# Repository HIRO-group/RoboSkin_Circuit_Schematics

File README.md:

# Robo-Skin Circuit Schematics

Below is the schematic file:

Below is the Board file:

The gerber files will be in the CamOutput folder. The .sch file is the eagle schematics and .brd is the board file. 

The schematics contain circuit in human readable format

The board files contain circuit which can be etched on a copper sheet, basically the final how circuit board looks like

You can install final gerber files like this:

```bash
sudo apt install gerbv
gerbv GERBER_FILE_PATH
```

Modifications and suggestions are highly appreciated. Be sure to give a PR.

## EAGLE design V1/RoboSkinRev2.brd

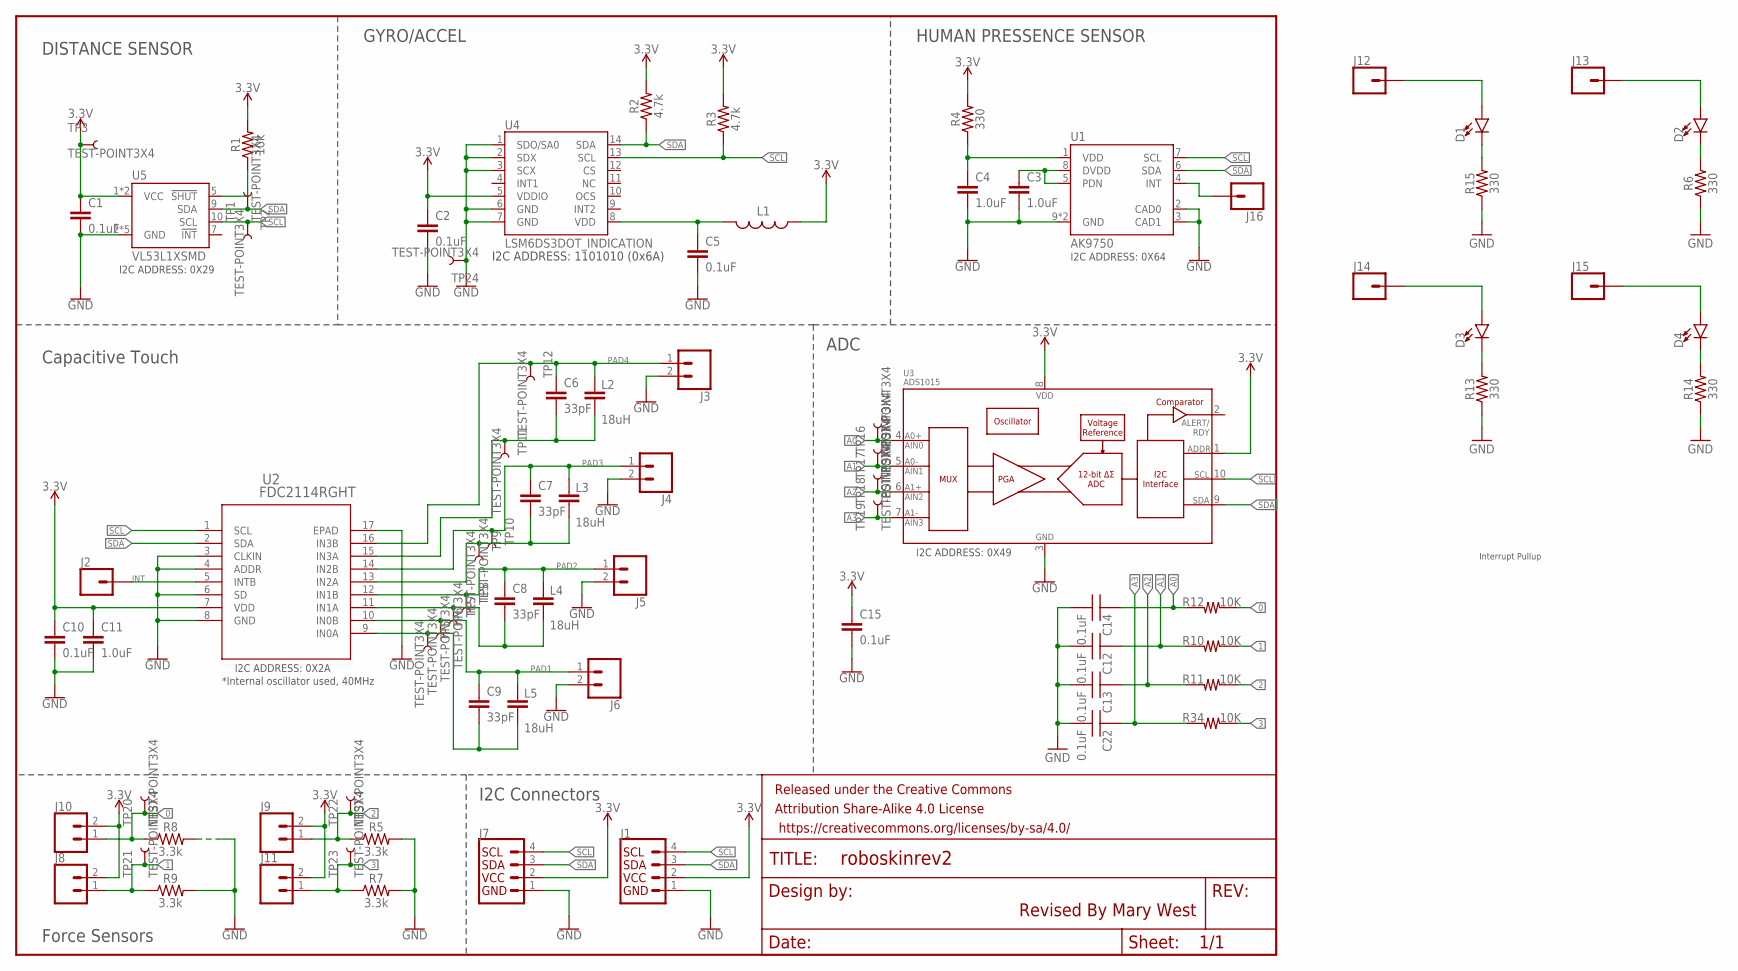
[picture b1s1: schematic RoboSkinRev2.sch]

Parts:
C1, C2, C5, C10, C15: 0.1uF; 0603
C3, C4, C11: 1.0uF; 0603
C6, C7, C8, C9: 33pF; 0603
C12, C13, C14, C22: 0.1uF; 0603_SILK; PARTNO GRM188R70J104KA01D
D1, D2, D3, D4: LED1206; LED-1206
FRAME1: FRAME-LETTERNO_PACKAGE; DUMMY
J1, J7: QWIIC_CONNECTORJS-1MM; 1X04_1MM_RA
J2, J12, J13, J14, J15: CONN_01; 1X01
J3, J4, J5, J6, J8, J9, J10, J11: CONN_02; 1X02
J16: CONN_01PTH_NO_SILK_YES_STOP; 1X01_NO_SILK
L1: RES-07859; 0603
L2, L3, L4, L5: 18uH; 1210
R1: 10k; 0603
R2, R3: 4.7k; 0603
R4, R6, R13, R14, R15: 330; 0603
R5, R7, R8, R9: 3.3k; 0603
R10, R11, R12, R34: 10K; 0603_SILK; PARTNO CR0603-FX-1002ELF
TP1, TP2, TP3, TP5, TP6, TP7, TP8, TP9, TP10, TP11, TP12, TP16, TP17, TP18, TP19, TP20, TP21, TP22, TP23, TP24: TEST-POINT3X4; PAD.03X.04
U1: AK9750; SON10
U2: FDC2114RGHT; RGH16
U3: ADS1015; MSOP10
U4: LSM6DS3DOT_INDICATION; LGA14L_DOT_INDICATOR
U5: VL53L1XSMD; VL53L1X

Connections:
0: J10.1, R8.1, R12.P2 (2), TP20.P$1
1: J8.1, R9.1, R10.P2 (2), TP21.P$1
2: J9.1, R5.1, R11.P2 (2), TP22.P$1
3: J11.1, R7.1, R34.P2 (2), TP23.P$1
3.3V: C1.1, C2.1, C10.1, C11.1, C15.1, J1.2 (VCC), J7.2 (VCC), J8.2, J9.2, J10.2, J11.2, L1.1, R1.2, R2.2, R3.2, R4.2, TP3.P$1, U2.7 (VDD), U3.1 (ADDR), U3.8 (VDD), U4.5 (VDDIO), U5.1 (VCC), U5.11 (VCC)
A0: C14.P1 (1), R12.P1 (1), TP16.P$1, U3.4 (AIN0)
A1: C12.P1 (1), R10.P1 (1), TP17.P$1, U3.5 (AIN1)
A2: C13.P1 (1), R11.P1 (1), TP18.P$1, U3.6 (AIN2)
A3: C22.P1 (1), R34.P1 (1), TP19.P$1, U3.7 (AIN3)
D1: D2.A, J13.1
D2: D3.A, J14.1
D3: D4.A, J15.1
D7: D1.A, J12.1
GND: C1.2, C2.2, C3.2, C4.2, C5.2, C10.2, C11.2, C12.P2 (2), C13.P2 (2), C14.P2 (2), C15.2, C22.P2 (2), J1.1 (GND), J3.2, J4.2, J5.2, J6.2, J7.1 (GND), R5.2, R6.1, R7.2, R8.2, R9.2, R13.1, R14.1, R15.1, TP24.P$1, U1.2 (CAD0), U1.3 (CAD1), U1.9 (GND), U1.10 (GND), U2.3 (CLKIN), U2.4 (ADDR), U2.6 (SD), U2.8 (GND), U2.17 (EPAD), U3.3 (VSS), U4.1 (SDO/SA0), U4.2 (SDX), U4.3 (SCX), U4.6 (GND), U4.7 (GND), U5.2 (GND), U5.3 (GND), U5.4 (GND), U5.6 (GND), U5.12 (GND)
INT: J2.1, U2.5 (INTB)
unnamed: C4.1, R4.1, U1.1 (VDD)
unnamed: C3.1, U1.5 (PDN), U1.8 (DVDD)
unnamed: R1.1, U5.5 (!SHUT)
unnamed: D1.C, R15.2
unnamed: D2.C, R6.2
unnamed: C5.1, L1.2, U4.8 (VDD)
unnamed: D3.C, R13.2
unnamed: C6.2, L2.2, TP11.P$1, U2.15 (IN3A)
unnamed: D4.C, R14.2
unnamed: C7.2, L3.2, TP9.P$1, U2.13 (IN2A)
unnamed: J16.1, U1.4 (INT)
unnamed: C8.2, L4.2, TP7.P$1, U2.11 (IN1A)
unnamed: C9.2, L5.2, TP5.P$1, U2.9 (IN0A)
PAD1: C9.1, J6.1, L5.1, TP6.P$1, U2.10 (IN0B)
PAD2: C8.1, J5.1, L4.1, TP8.P$1, U2.12 (IN1B)
PAD3: C7.1, J4.1, L3.1, TP10.P$1, U2.14 (IN2B)
PAD4: C6.1, J3.1, L2.1, TP12.P$1, U2.16 (IN3B)
SCL: J1.4 (SCL), J7.4 (SCL), R3.1, TP2.P$1, U1.7 (SCL), U2.1 (SCL), U3.10 (SCL), U4.13 (SCL), U5.10 (SCL)
SDA: J1.3 (SDA), J7.3 (SDA), R2.1, TP1.P$1, U1.6 (SDA), U2.2 (SDA), U3.9 (SDA), U4.14 (SDA), U5.9 (SDA)

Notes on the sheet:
I2C ADDRESS: 1101010 (0x6A)
Revised By Mary West
I2C ADDRESS: 0X29
I2C ADDRESS: 0X64
HUMAN PRESSENCE SENSOR
GYRO/ACCEL
DISTANCE SENSOR
Capacitive Touch
I2C ADDRESS: 0X2A
*Internal oscillator used, 40MHz
I2C ADDRESS: 0X49
I2C Connectors
Force Sensors
ADC
Interrupt Pullup

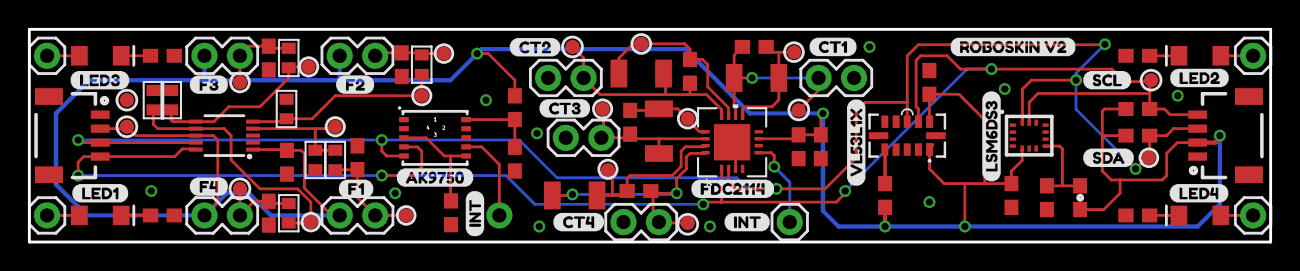
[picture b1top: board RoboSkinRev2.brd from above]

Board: 2 copper layers, 88.9 x 15.2 mm, 105 parts (1 on the bottom side), 34 nets.

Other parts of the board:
U$1: CAPTURE#PNG
U$24: AK975035
U$25: CT12
U$26: CT23
U$27: CT34
U$28: CT45
U$29: F16
U$30: F27
U$31: F38
U$32: F49
U$34: FDC211438
U$36, U$46: INT30
U$37: LED131
U$38: LED232
U$39: LED333
U$40: LED434
U$41: LSM6DS336
U$42: ROBOSKIN_V241
U$43: SCL39
U$44: SDA40
U$45: VL53L1X37

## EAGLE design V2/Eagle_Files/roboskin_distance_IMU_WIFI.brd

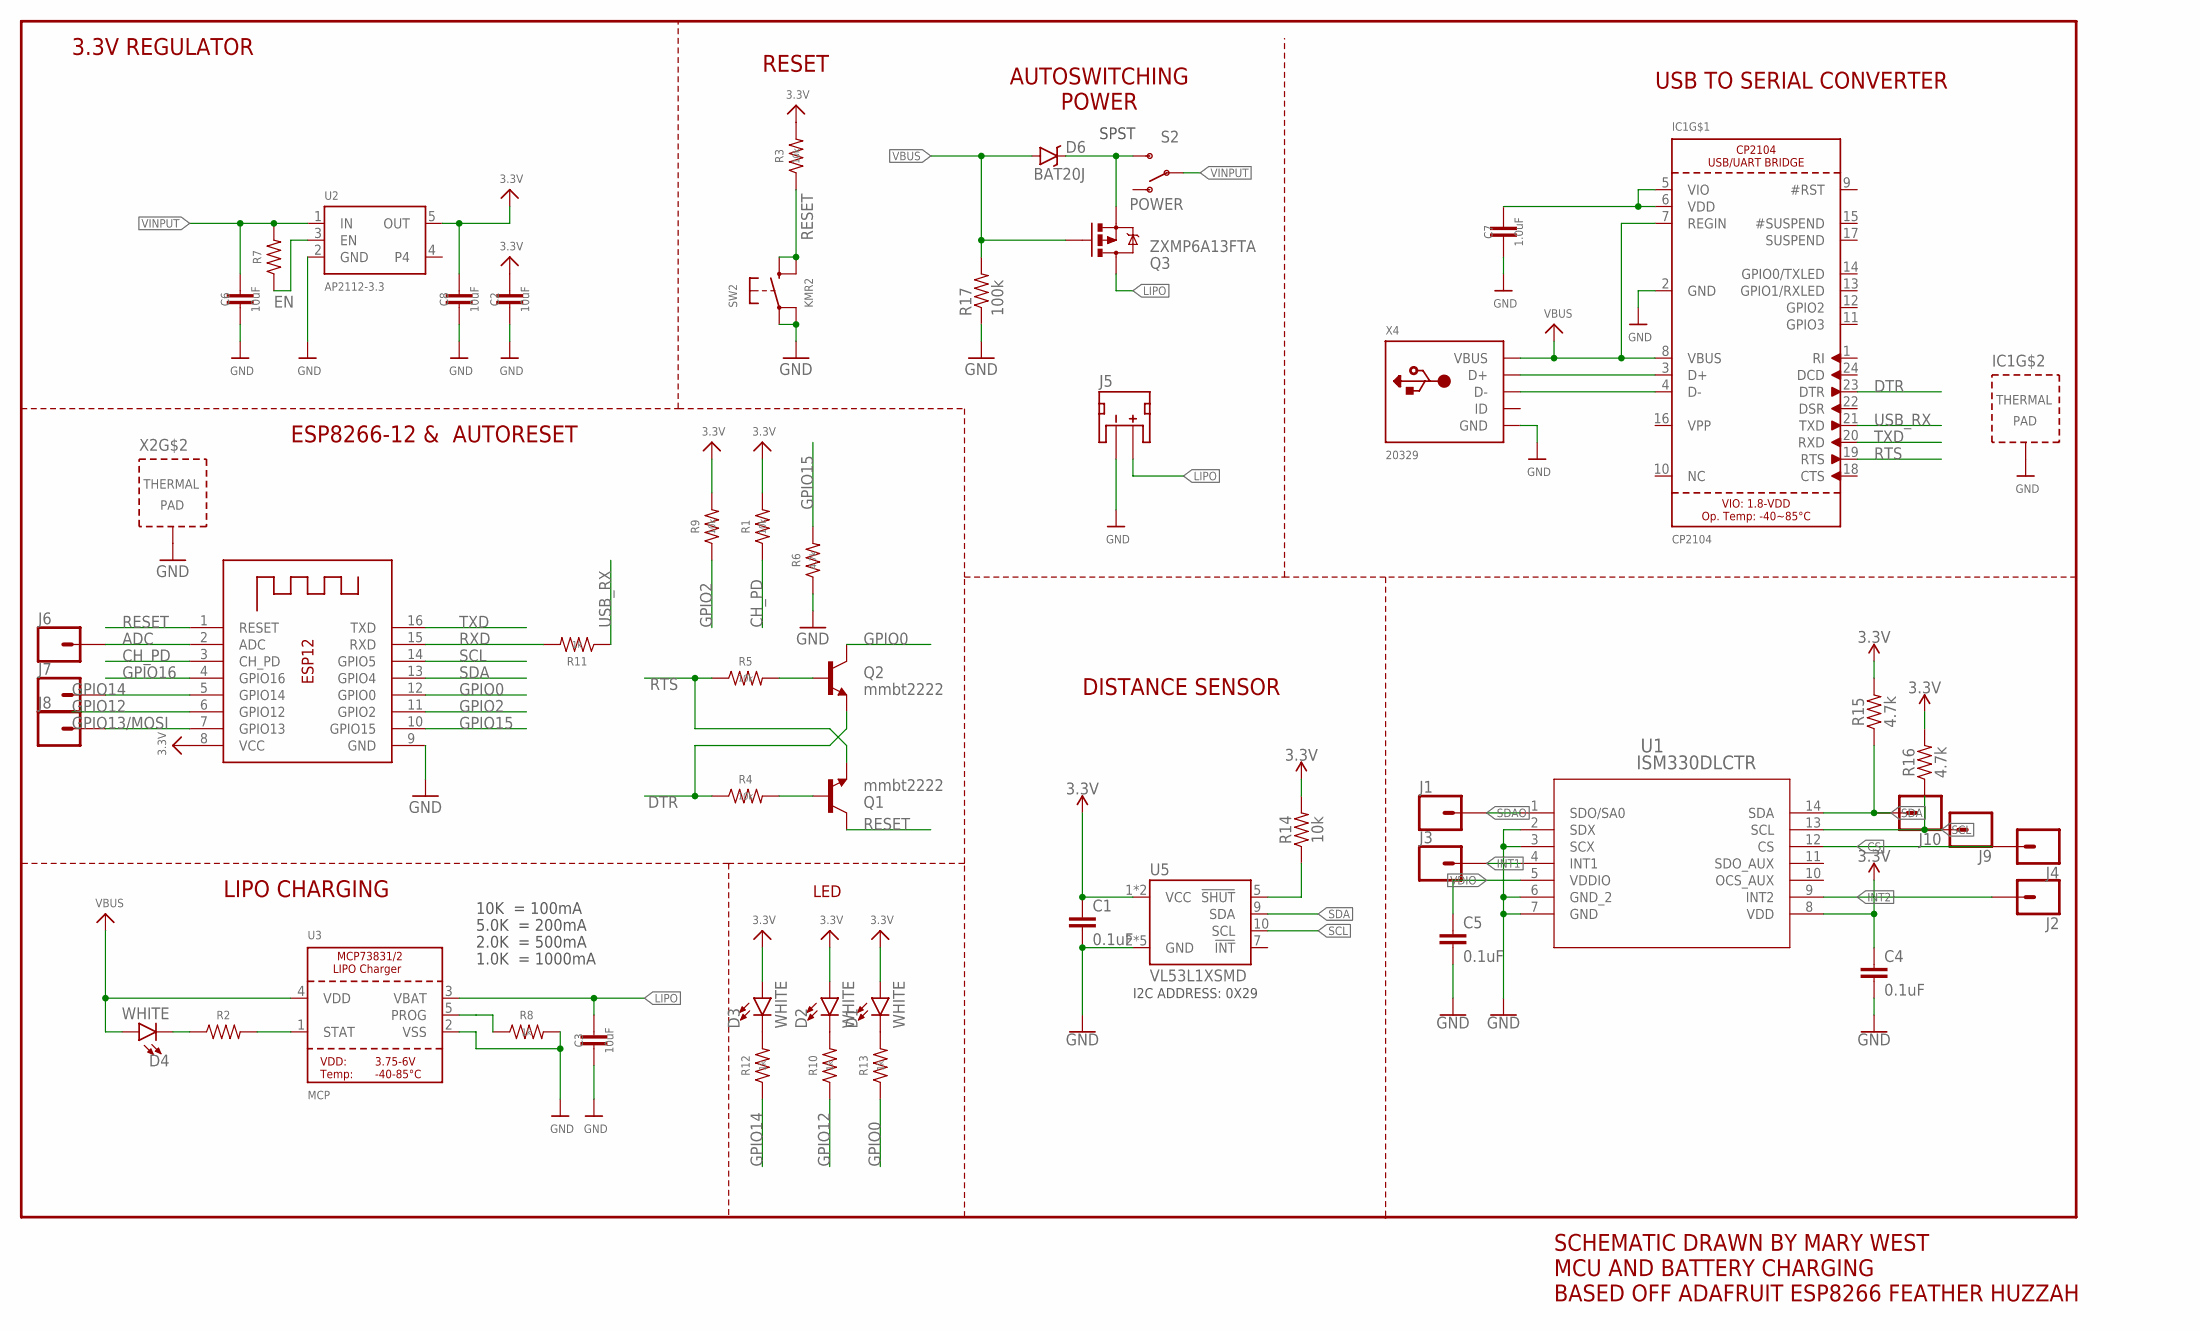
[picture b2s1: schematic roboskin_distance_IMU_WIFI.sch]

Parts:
C1, C4, C5: 0.1uF; 0603
C2, C3, C6, C8: 10uF; 0805
C7: 1.0uF; 0603
D1, D2, D3, D4: WHITE; LED-1206
D6: BAT20J; SOD-323
IC1: CP2104; QFN24_4MM_SMSC
J1, J2, J3, J4, J6, J7, J8, J9, J10: CONN_01; 1X01
J5: JST_2MM_MALE; JST-2-SMD
Q1, Q2: mmbt2222; SOT23-3
Q3: ZXMP6A13FTA; SOT23-3
R1, R3, R4, R5, R7, R9, R14: 10k; 0603
R2, R8, R10, R11, R12, R13: 1k; 0603
R6, R15, R16: 4.7k; 0603
R17: 100k; 0603-RES
S2: POWER; SWITCH-SPST-SMD-A
SW2: KMR2; BTN_KMR2_4.6X2.8
U1: ISM330DLCTR; LGA-14L_2P5X3X0P83_STM
U2: AP2112-3.3; SOT23-5
U3: MCP; SOT23-5
U5: VL53L1XSMD; VL53L1X
X2: ESP-12; ESP-12S
X4: 20329; 4UCONN_20329_V2

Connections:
3.3V: C1.1, C2.1, C4.1, C8.1, D1.A, D2.A, D3.A, R1.2, R3.2, R9.2, R14.2, R15.2, R16.2, U1.8 (VDD), U2.5 (OUT), U5.1 (VCC), U5.11 (VCC), X2.8 (VCC)
ADC: J6.1, X2.2 (ADC)
CH_PD: R1.1, X2.3 (CH_PD)
CS: J4.1, U1.12 (CS)
DTR: IC1.23 (DTR), Q2.2 (E), R4.1
EN: R7.1, U2.3 (EN)
GND: C1.2, C2.2, C3.2, C4.2, C5.2, C6.2, C7.2, C8.2, IC1.2 (GND), IC1.THERM (TP), J5.1 (-), R6.1, R8.2, R17.1, SW2.A, SW2.A' (P1), U1.2 (SDX), U1.3 (SCX), U1.6 (GND_2), U1.7 (GND), U2.2 (GND), U3.2 (VSS), U5.2 (GND), U5.3 (GND), U5.4 (GND), U5.6 (GND), U5.12 (GND), X2.9 (GND), X2.P$1 (TP), X4.BASE@1 (GND), X4.BASE@2 (GND), X4.GND, X4.SPRT@1 (GND), X4.SPRT@2 (GND), X4.SPRT@3 (GND), X4.SPRT@4 (GND)
GPIO0: Q2.3 (C), R13.1, X2.12 (GPIO0)
GPIO2: R9.1, X2.11 (GPIO2)
GPIO12: R10.1, X2.6 (GPIO12)
GPIO13/MOSI: J8.1, X2.7 (GPIO13)
GPIO14: J7.1, R12.1, X2.5 (GPIO14)
GPIO15: R6.2, X2.10 (GPIO15)
GPIO16: X2.4 (GPIO16)
INMOSFET: D6.C, Q3.2 (S), S2.3 (S)
INT1: J3.1, U1.4 (INT1)
INT2: J2.1, U1.9 (INT2)
LIPO: C3.1, J5.2 (+), Q3.3 (D), U3.3 (VBAT)
unnamed: D4.C, R2.1
unnamed: IC1.3 (D+), X4.D+
unnamed: R2.2, U3.1 (STAT)
unnamed: R8.1, U3.5 (PROG)
unnamed: D1.C, R13.2
unnamed: IC1.4 (D-), X4.D-
unnamed: D2.C, R10.2
unnamed: C7.1, IC1.5 (VIO), IC1.6 (VDD)
unnamed: D3.C, R12.2
unnamed: R14.1, U5.5 (!SHUT)
unnamed: Q1.1 (B), R4.2
unnamed: Q2.1 (B), R5.2
RESET: Q1.3 (C), R3.1, SW2.B (S), SW2.B' (S1), X2.1 (RESET)
RTS: IC1.19 (RTS), Q1.2 (E), R5.1
RXD: R11.2, X2.15 (RXD)
SCL: J9.1, R16.1, U1.13 (SCL), U5.10 (SCL), X2.14 (GPIO5)
SDA: J10.1, R15.1, U1.14 (SDA), U5.9 (SDA), X2.13 (GPIO4)
SDAO: J1.1, U1.1 (SDO/SA0)
TXD: IC1.20 (RXD), X2.16 (TXD)
USB_RX: IC1.21 (TXD), R11.1
VBUS: D4.A, D6.A, IC1.7 (REGIN), IC1.8 (VBUS), Q3.1 (G), R17.2, U3.4 (VDD), X4.VBUS
VDIO: C5.1, U1.5 (VDDIO)
VINPUT: C6.1, R7.2, S2.2, U2.1 (IN)

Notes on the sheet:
3.3V REGULATOR
RESET
10K = 100mA
5.0K = 200mA
2.0K = 500mA
1.0K = 1000mA
USB TO SERIAL CONVERTER
LIPO CHARGING
LED
ESP8266-12 & AUTORESET
I2C ADDRESS: 0X29
DISTANCE SENSOR
SCHEMATIC DRAWN BY MARY WEST MCU AND BATTERY CHARGING BASED OFF ADAFRUIT ESP8266 FEATHER HUZZAH
SPST
AUTOSWITCHING POWER

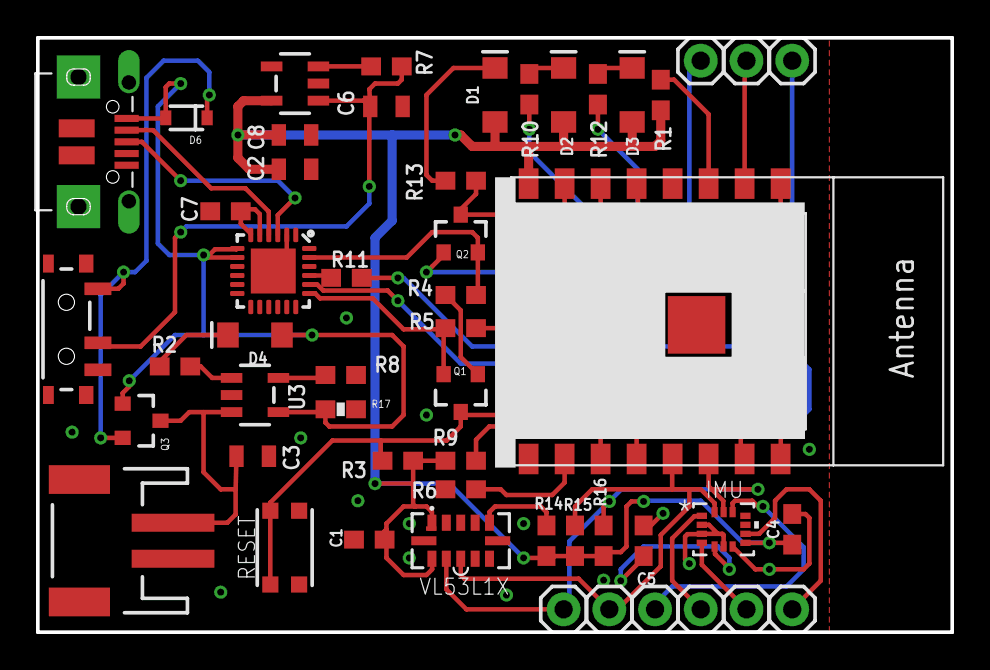
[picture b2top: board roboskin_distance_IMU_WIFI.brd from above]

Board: 2 copper layers, 50.8 x 33.0 mm, 53 parts (1 on the bottom side), 40 nets.

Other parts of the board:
U$6: HIRO_GRAPHICS#PNG

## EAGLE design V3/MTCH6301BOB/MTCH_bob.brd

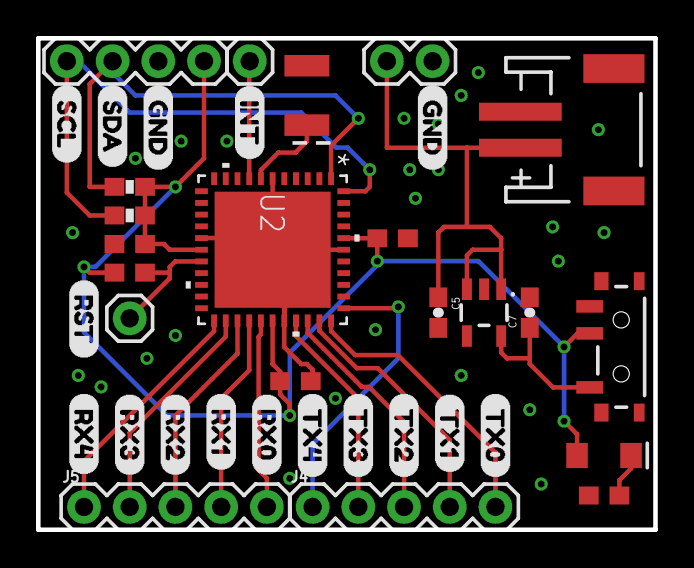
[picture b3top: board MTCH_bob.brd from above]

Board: 2 copper layers, 34.3 x 27.3 mm, 38 parts (0 on the bottom side), 20 nets.

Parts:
C1, C2, C3: 0.1uF; 0603
C4: 10uF; EIA3528
C5: 1uF; 0603-CAP
C7: 2.2uF; 0603-CAP
D4: RED; LED-1206
FRAME1: FRAME-LETTERNO_PACKAGE; DUMMY
J1: 1X04
J2: LiPo; JST-2-SMD
J3, J7: 1X01
J4, J5: 1X05
J6: 1X02
R1: 20k; 0603
R2: 1k; 0603
R11, R12: 4.7K; 0603-RES
S1: POWER; SWITCH-SPST-SMD-A
U2: MTCH6301-I/ML; QFN44_8X8MC_MCH
U4: AP2112K-3.3TRG-1; SOT23-5
U$1, U$16: GND0
U$2: INT12
U$3: RST15
U$4: RX07
U$5: RX18
U$6: RX29
U$7: RX310
U$8: RX411
U$9: SCL14
U$10: SDA13
U$11: TX02
U$12: TX13
U$14: TX35
U$15: TX46
U$17: TX24

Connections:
GND: C1.2, C2.2, C3.2, C4.C, C5.2, C7.2, J1.3, J2.1, J6.1, R2.1, U2.6, U2.16, U2.29, U2.39, U2.45, U4.2, U4.4
INT: J3.1, U2.8
LIPO: C5.1, J2.2, J6.2, U4.1, U4.3
unnamed: C4.A, U2.7
unnamed: D4.C, R2.2
RST: J7.1, R1.1, U2.18
RX0: J5.5, U2.27
RX1: J5.4, U2.26
RX2: J5.3, U2.25
RX3: J5.2, U2.24
RX4: J5.1, U2.23
SCL: J1.1, R12.1, U2.44
SDA: J1.2, R11.1, U2.1
TX0: J4.5, U2.33
TX1: J4.4, U2.32
TX2: J4.3, U2.31
TX3: J4.2, U2.30
TX4: J4.1, U2.34
VCC: C1.1, C2.1, C3.1, D4.A, J1.4, R1.2, R11.2, R12.2, S1.2, U2.17, U2.28, U2.40
VOUT: C7.1, S1.3, U4.5

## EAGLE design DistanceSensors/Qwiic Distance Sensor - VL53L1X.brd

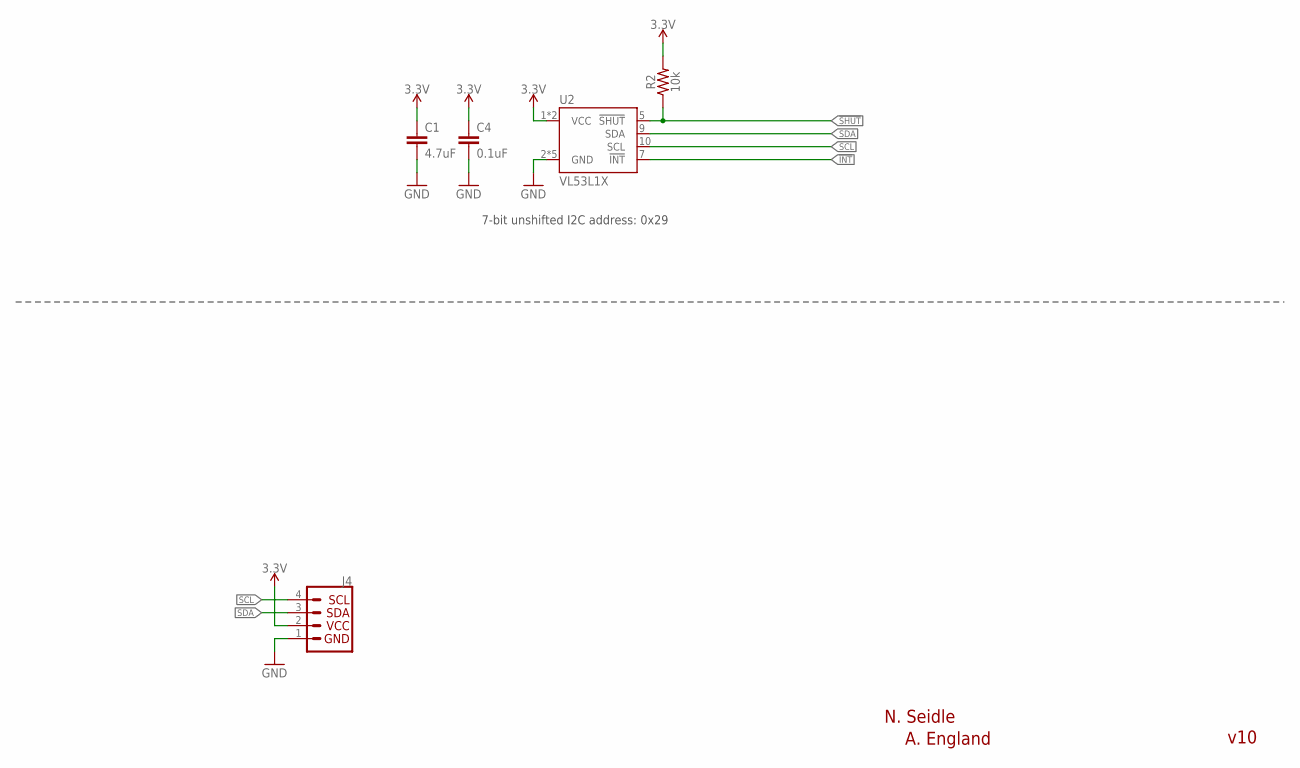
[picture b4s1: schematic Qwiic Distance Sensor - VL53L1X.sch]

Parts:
C1: 4.7uF; 0603
C4: 0.1uF; 0603
J4: QWIIC_CONNECTORJS-1MM; 1X04_1MM_RA
R2: 10k; 0603
U2: VL53L1X

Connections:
3.3V: C1.1, C4.1, J4.2, R2.2, U2.1 (VCC), U2.11 (VCC)
!INT: U2.7 (!INT)
!SHUT: R2.1, U2.5 (!SHUT)
GND: C1.2, C4.2, J4.1, U2.2 (GND), U2.3 (GND), U2.4 (GND), U2.6 (GND), U2.12 (GND)
SCL: J4.4, U2.10 (SCL)
SDA: J4.3, U2.9 (SDA)

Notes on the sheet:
N. Seidle
v10
7-bit unshifted I2C address: 0x29
A. England

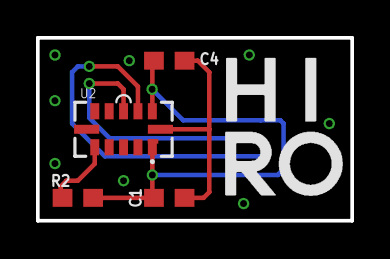
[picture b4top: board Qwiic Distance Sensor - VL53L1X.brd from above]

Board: 2 copper layers, 17.5 x 10.2 mm, 6 parts (1 on the bottom side), 5 nets.

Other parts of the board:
U$1: HIRO#PNG

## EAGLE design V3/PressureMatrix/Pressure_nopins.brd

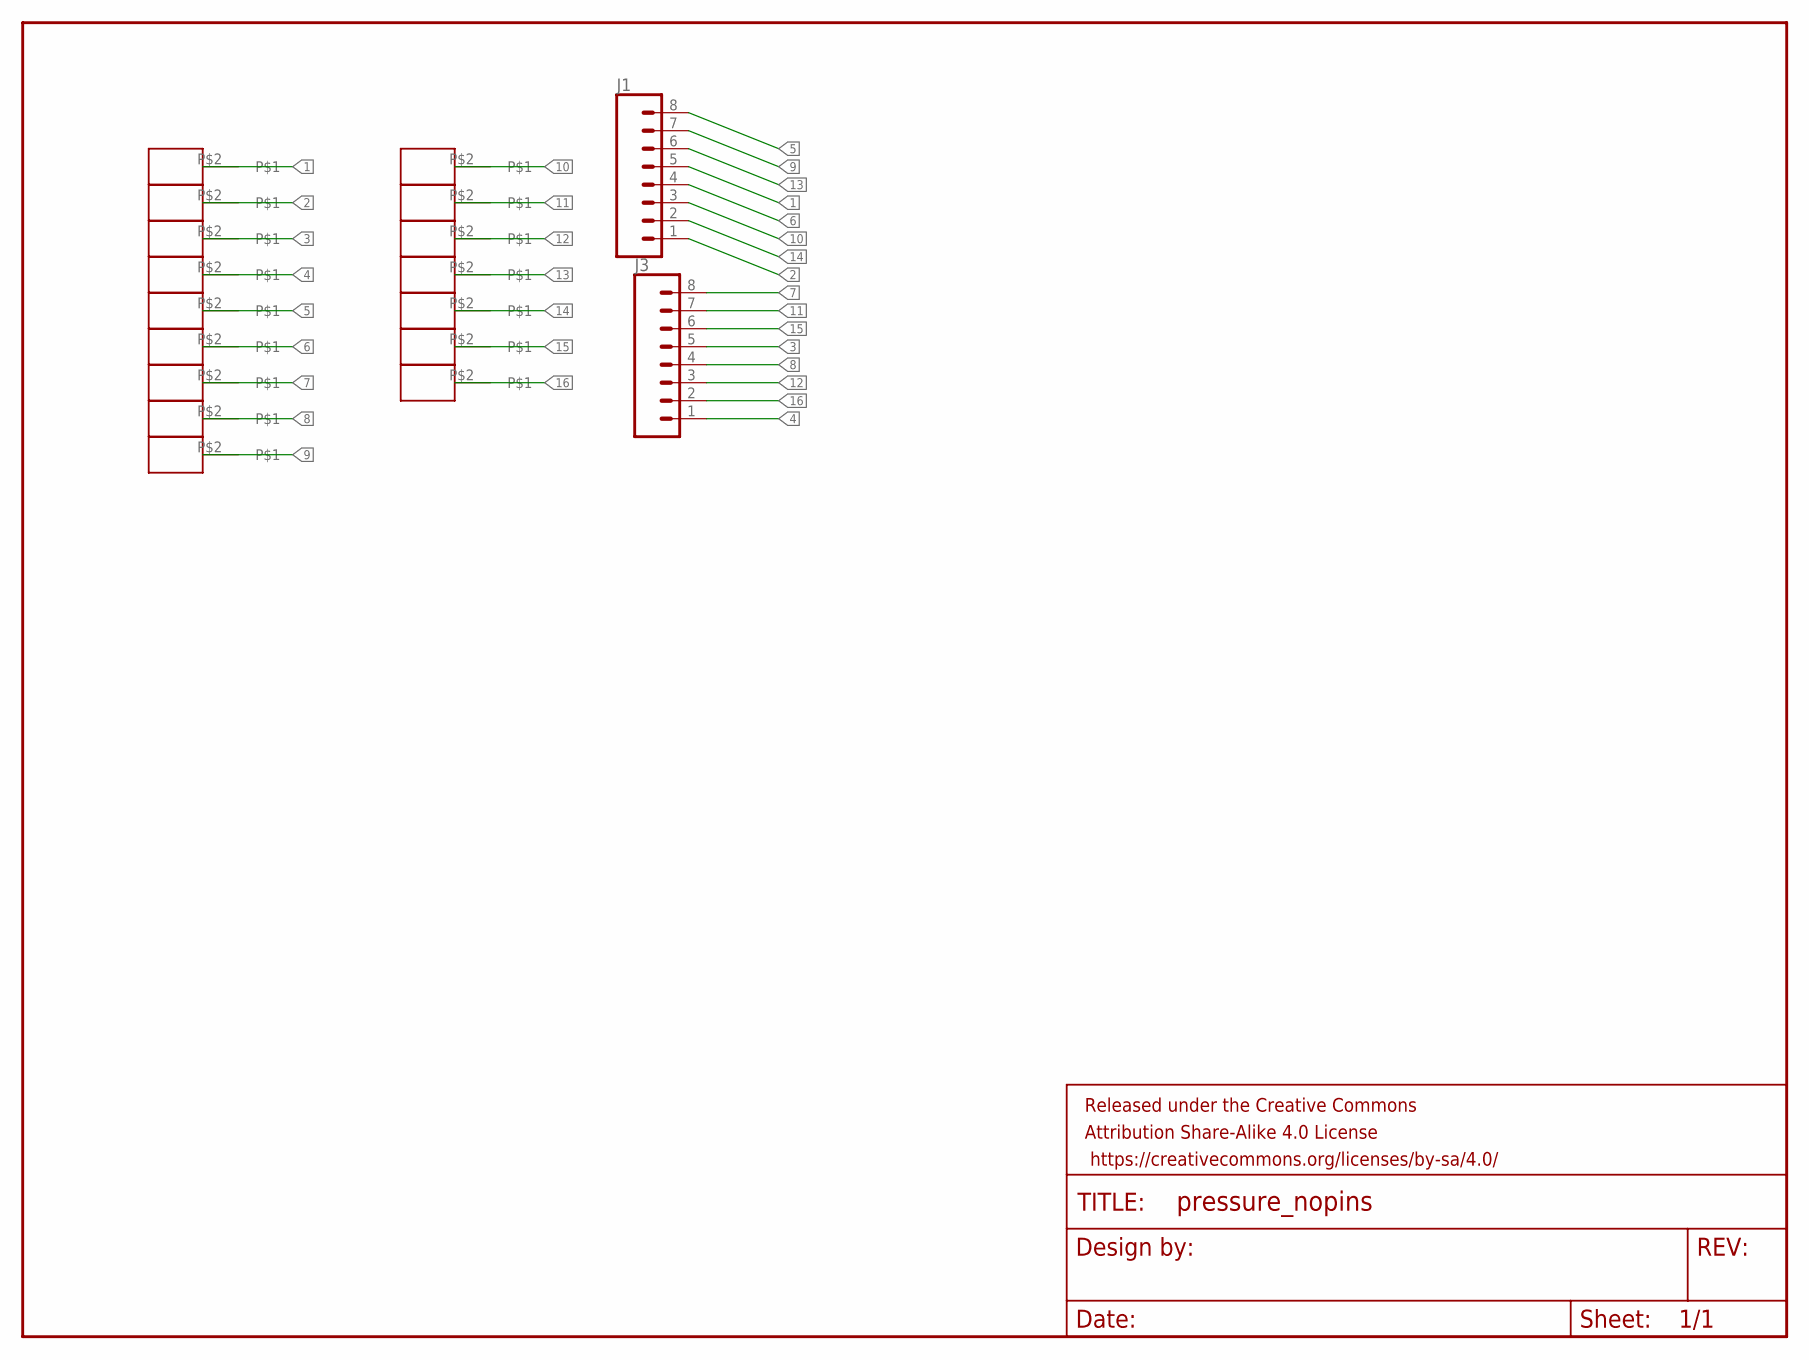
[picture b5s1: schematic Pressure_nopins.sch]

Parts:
FRAME1: FRAME-LETTERNO_PACKAGE; DUMMY
J1, J3: CONN_08SMD-MALE; 1X08_SMD_MALE
U$1, U$2, U$3, U$4, U$5, U$6, U$7, U$8, U$9, U$10, U$11, U$12, U$13, U$14, U$15, U$16: 250MIL_1X1

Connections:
1: J1.5, U$1.P$2
2: J1.1, U$2.P$2
3: J3.5, U$3.P$2
4: J3.1, U$4.P$2
5: J1.8, U$5.P$2
6: J1.4, U$6.P$2
7: J3.8, U$7.P$2
8: J3.4, U$8.P$2
9: J1.7, U$9.P$2
10: J1.3, U$10.P$2
11: J3.7, U$11.P$2
12: J3.3, U$12.P$2
13: J1.6, U$13.P$2
14: J1.2, U$14.P$2
15: J3.6, U$15.P$2
16: J3.2, U$16.P$2

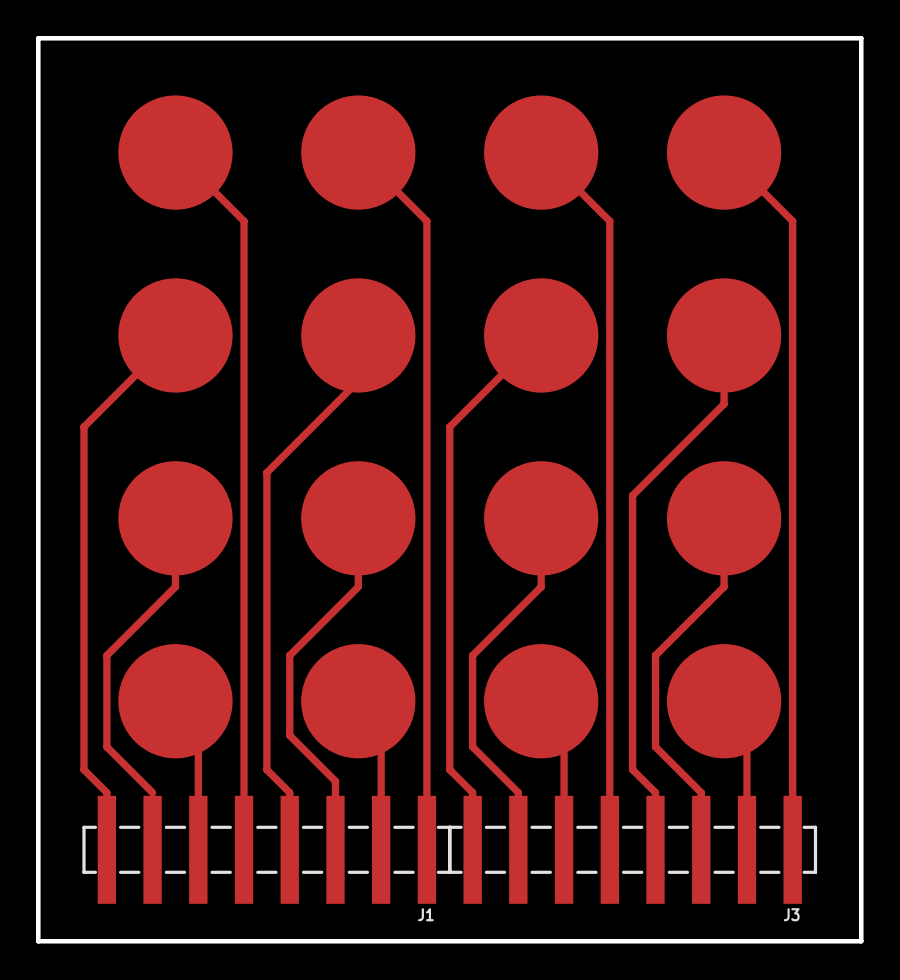
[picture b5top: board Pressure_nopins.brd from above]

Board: 2 copper layers, 45.7 x 50.2 mm, 19 parts (0 on the bottom side), 16 nets.

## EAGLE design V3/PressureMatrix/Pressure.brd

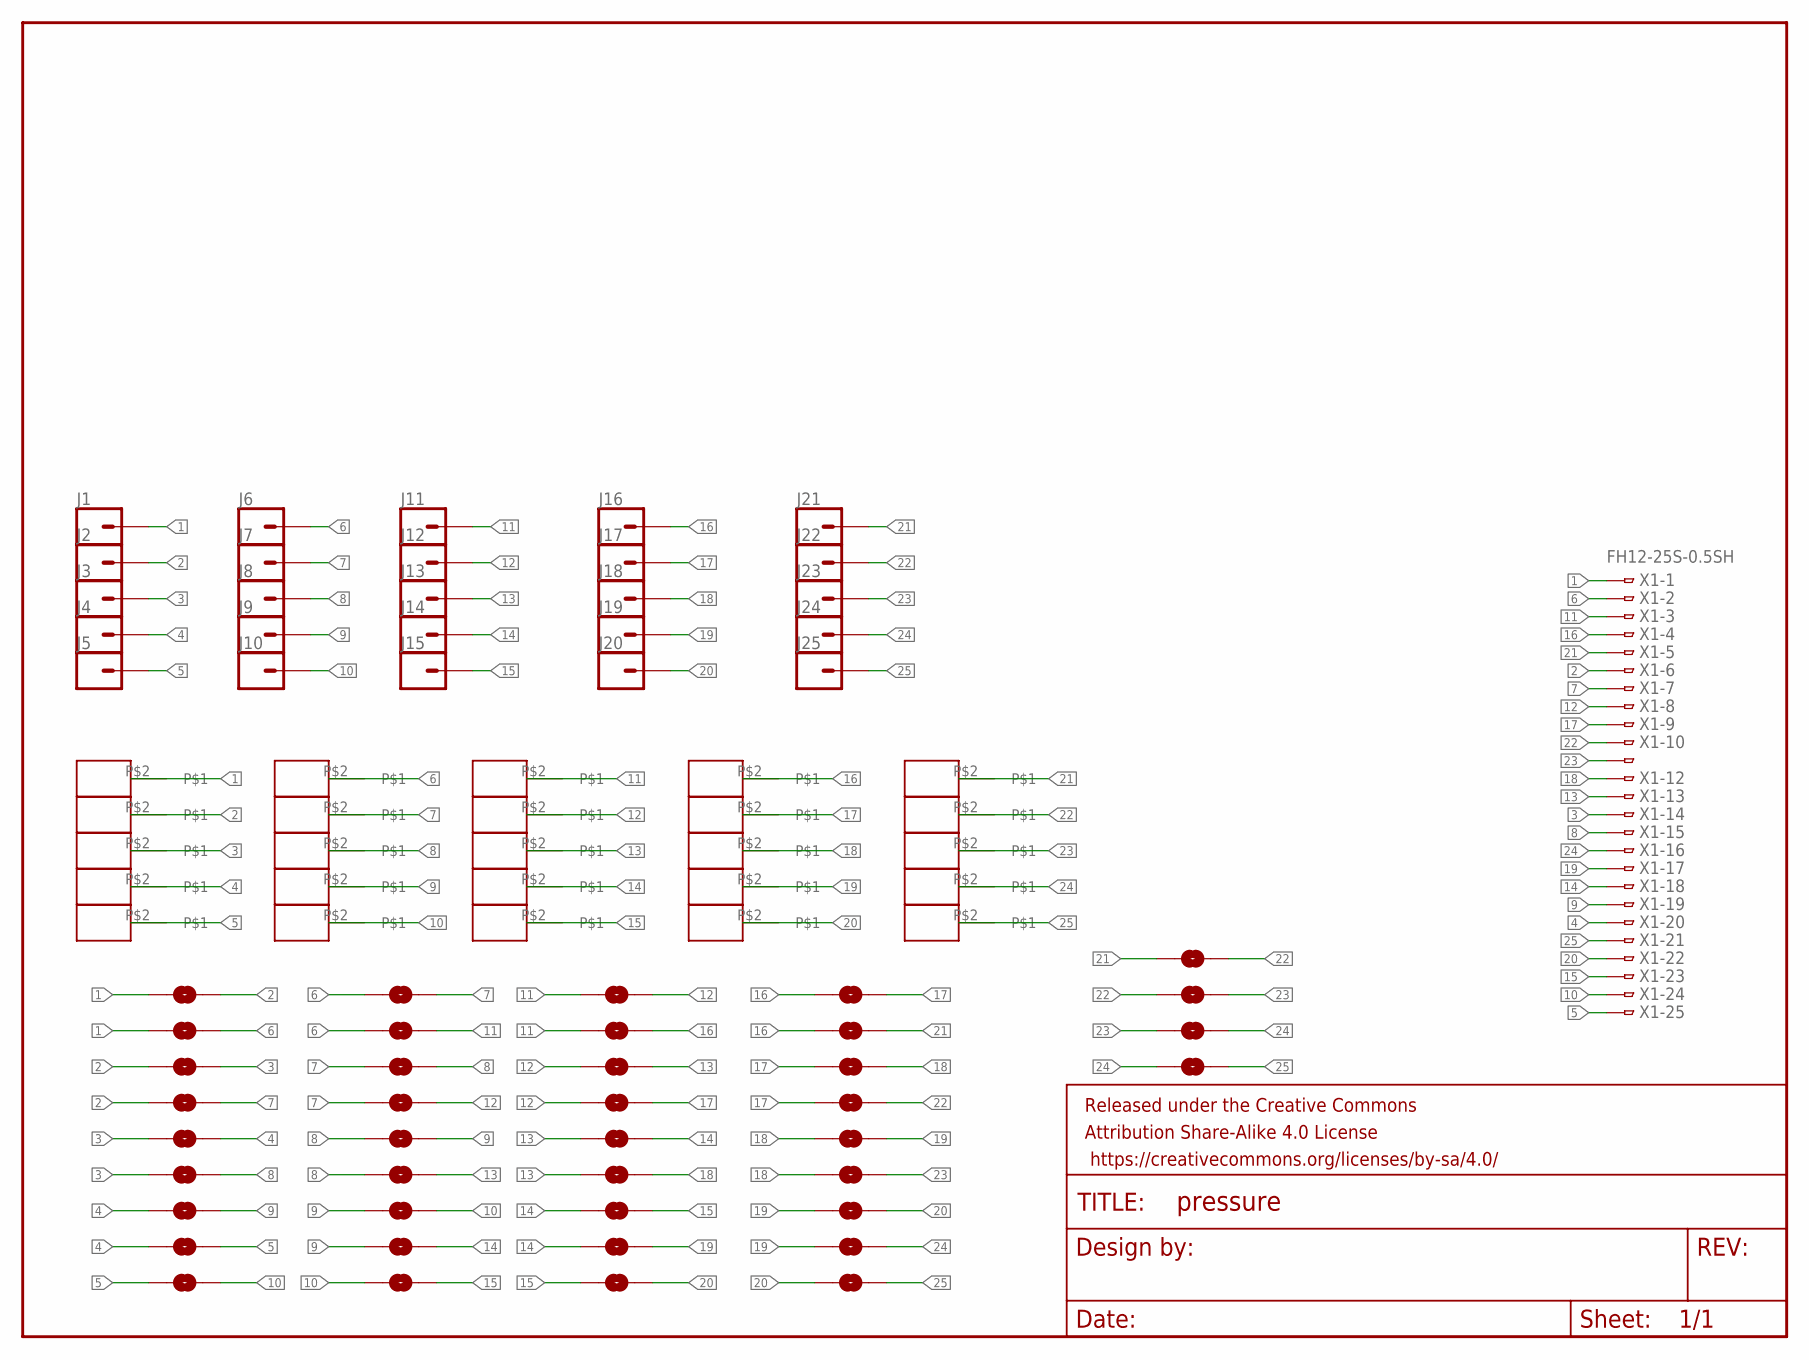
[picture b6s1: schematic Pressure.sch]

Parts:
FRAME1: FRAME-LETTERNO_PACKAGE; DUMMY
J1, J2, J3, J4, J5, J6, J7, J8, J9, J10, J11, J12, J13, J14, J15, J16, J17, J18, J19, J20, J21, J22, J23, J24, J25: CONN_01PTH_NO_SILK_YES_STOP; 1X01_NO_SILK
JP1, JP2, JP3, JP4, JP5, JP6, JP7, JP8, JP9, JP10, JP11, JP12, JP13, JP14, JP15, JP16, JP17, JP18, JP19, JP20, JP21, JP22, JP23, JP24, JP25, JP26, JP27, JP28, JP29, JP30, JP31, JP32, JP33, JP34, JP35, JP36, JP37, JP38, JP39, JP40: JUMPER-SMT_2_NO_NO-SILK; SMT-JUMPER_2_NO_NO-SILK
U$1, U$2, U$3, U$4, U$5, U$6, U$7, U$8, U$9, U$10, U$11, U$12, U$13, U$14, U$15, U$16, U$17, U$18, U$19, U$20, U$21, U$22, U$23, U$24, U$25: 250MIL_1X1
X1: FH12-25S-0.5SH

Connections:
1: J1.1, JP1.1, JP2.1, U$1.P$2, X1.1
2: J2.1, JP1.2, JP3.1, JP4.1, U$2.P$2, X1.6
3: J3.1, JP3.2, JP5.1, JP6.1, U$3.P$2, X1.14
4: J4.1, JP5.2, JP7.1, JP8.1, U$4.P$2, X1.20
5: J5.1, JP8.2, JP9.1, U$5.P$2, X1.25
6: J6.1, JP2.2, JP10.1, JP11.1, U$6.P$2, X1.2
7: J7.1, JP4.2, JP10.2, JP12.1, JP13.1, U$7.P$2, X1.7
8: J8.1, JP6.2, JP12.2, JP14.1, JP15.1, U$8.P$2, X1.15
9: J9.1, JP7.2, JP14.2, JP16.1, JP17.1, U$9.P$2, X1.19
10: J10.1, JP9.2, JP16.2, JP18.1, U$10.P$2, X1.24
11: J11.1, JP11.2, JP19.1, JP20.1, U$11.P$2, X1.3
12: J12.1, JP13.2, JP19.2, JP21.1, JP22.1, U$12.P$2, X1.8
13: J13.1, JP15.2, JP21.2, JP23.1, JP24.1, U$13.P$2, X1.13
14: J14.1, JP17.2, JP23.2, JP25.1, JP26.1, U$14.P$2, X1.18
15: J15.1, JP18.2, JP25.2, JP27.1, U$15.P$2, X1.23
16: J16.1, JP20.2, JP28.1, JP29.1, U$16.P$2, X1.4
17: J17.1, JP22.2, JP28.2, JP30.1, JP31.1, U$17.P$2, X1.9
18: J18.1, JP24.2, JP30.2, JP32.1, JP33.1, U$18.P$2, X1.12
19: J19.1, JP26.2, JP32.2, JP34.1, JP35.1, U$19.P$2, X1.17
20: J20.1, JP27.2, JP34.2, JP36.1, U$20.P$2, X1.22
21: J21.1, JP29.2, JP37.1, U$21.P$2, X1.5
22: J22.1, JP31.2, JP37.2, JP38.1, U$22.P$2, X1.10
23: J23.1, JP33.2, JP38.2, JP39.1, U$23.P$2, X1.11
24: J24.1, JP35.2, JP39.2, JP40.1, U$24.P$2, X1.16
25: J25.1, JP36.2, JP40.2, U$25.P$2, X1.21

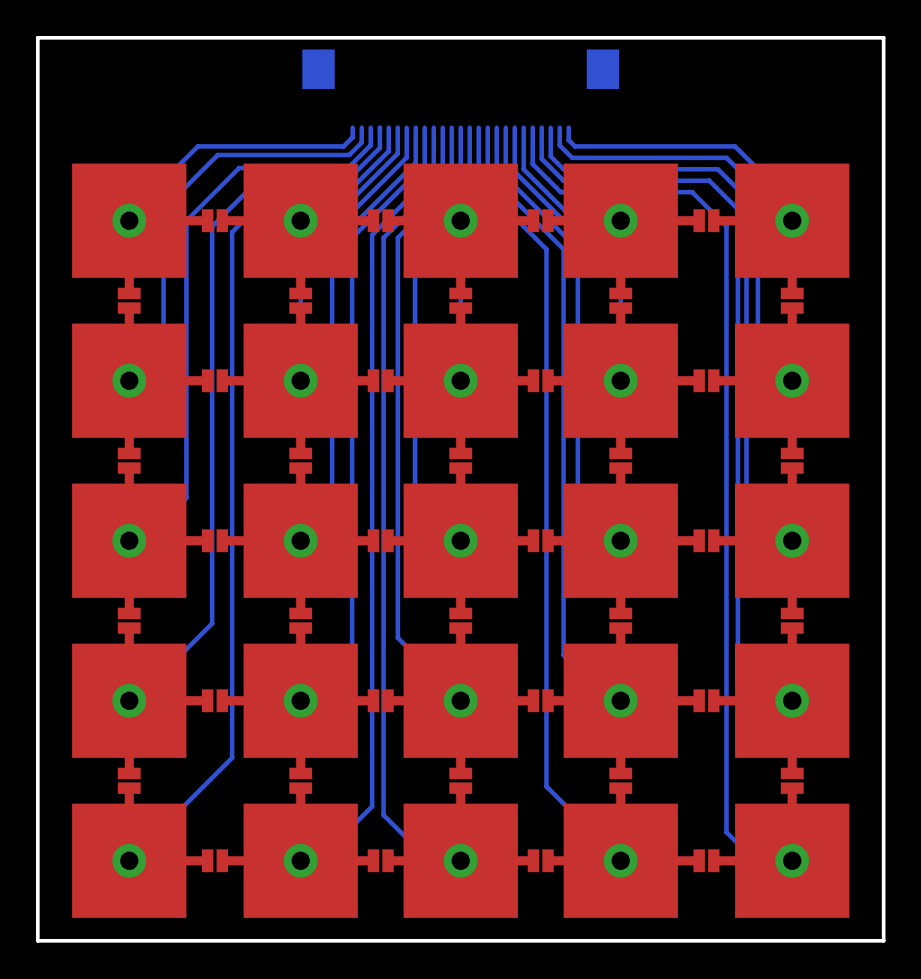
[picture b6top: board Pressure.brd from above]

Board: 2 copper layers, 47.0 x 50.2 mm, 92 parts (1 on the bottom side), 25 nets.

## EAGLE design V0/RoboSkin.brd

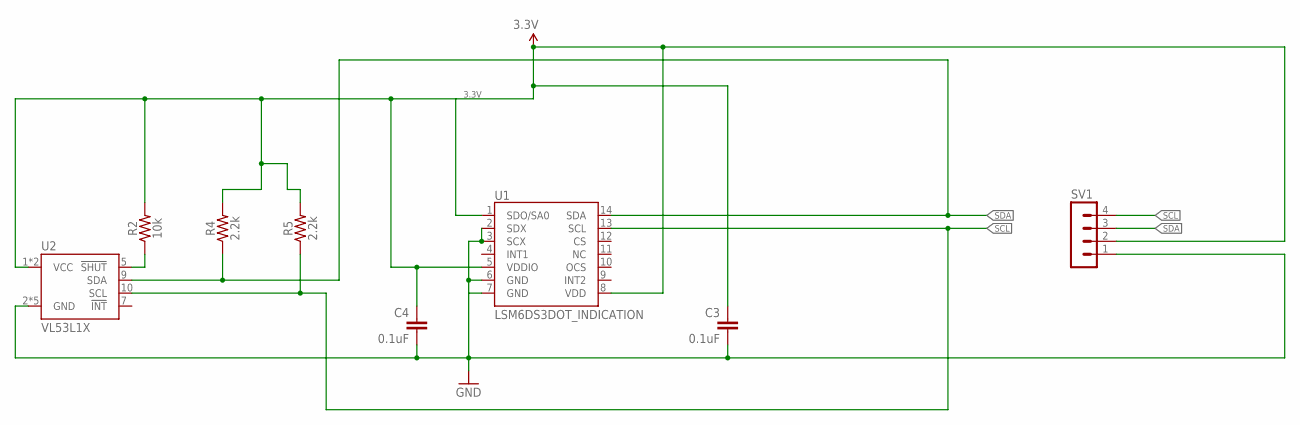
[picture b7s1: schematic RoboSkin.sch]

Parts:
C3, C4: 0.1uF; 0603-CAP
R2: 10k; 0603
R4, R5: 2.2k; 0603
SV1: MA04-1
U1: LSM6DS3DOT_INDICATION; LGA14L_DOT_INDICATOR
U2: VL53L1X

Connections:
3.3V: C3.1, C4.1, R2.2, R4.2, R5.2, SV1.2, U1.1 (SDO/SA0), U1.5 (VDDIO), U1.8 (VDD), U2.1 (VCC), U2.11 (VCC)
!SHUT: R2.1, U2.5 (!SHUT)
GND: C3.2, C4.2, SV1.1, U1.2 (SDX), U1.3 (SCX), U1.6 (GND), U1.7 (GND), U2.2 (GND), U2.3 (GND), U2.4 (GND), U2.6 (GND), U2.12 (GND)
SCL: R5.1, SV1.4, U1.13 (SCL), U2.10 (SCL)
SDA: R4.1, SV1.3, U1.14 (SDA), U2.9 (SDA)

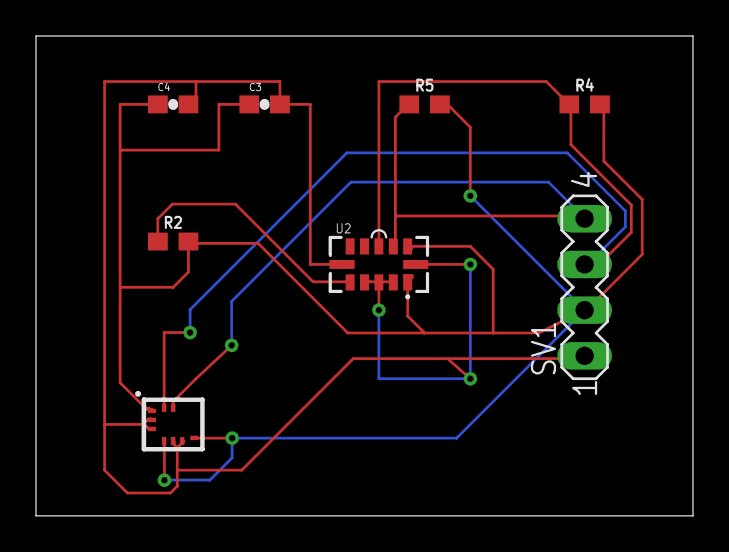
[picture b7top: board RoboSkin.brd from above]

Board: 2 copper layers, 36.5 x 26.7 mm, 8 parts (0 on the bottom side), 5 nets.

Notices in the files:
parts and their libraries:
SparkFun-Resistors: Licensing: Creative Commons ShareAlike 4.0 International - https://creativecommons.org/licenses/by-sa/4.0
COPYRIGHT: Copyright (C) 2018 Accelerated Designs. All rights reserved
SparkFun-Aesthetics: Released under the Creative Commons Attribution Share-Alike 4.0 License
